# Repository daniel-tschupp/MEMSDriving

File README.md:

# OCT MEMS Scanhead

As my second project in my master studies designed a 2d OCT MEMS Scanhead.

It contained three main tasks:
* Signal processing for drifing the MEMS
* Driver electronics design
* MCU Signal generation electronics design including Software

This repository contains the entier work including a documantaion in pdf format and the presentation as a video in german.

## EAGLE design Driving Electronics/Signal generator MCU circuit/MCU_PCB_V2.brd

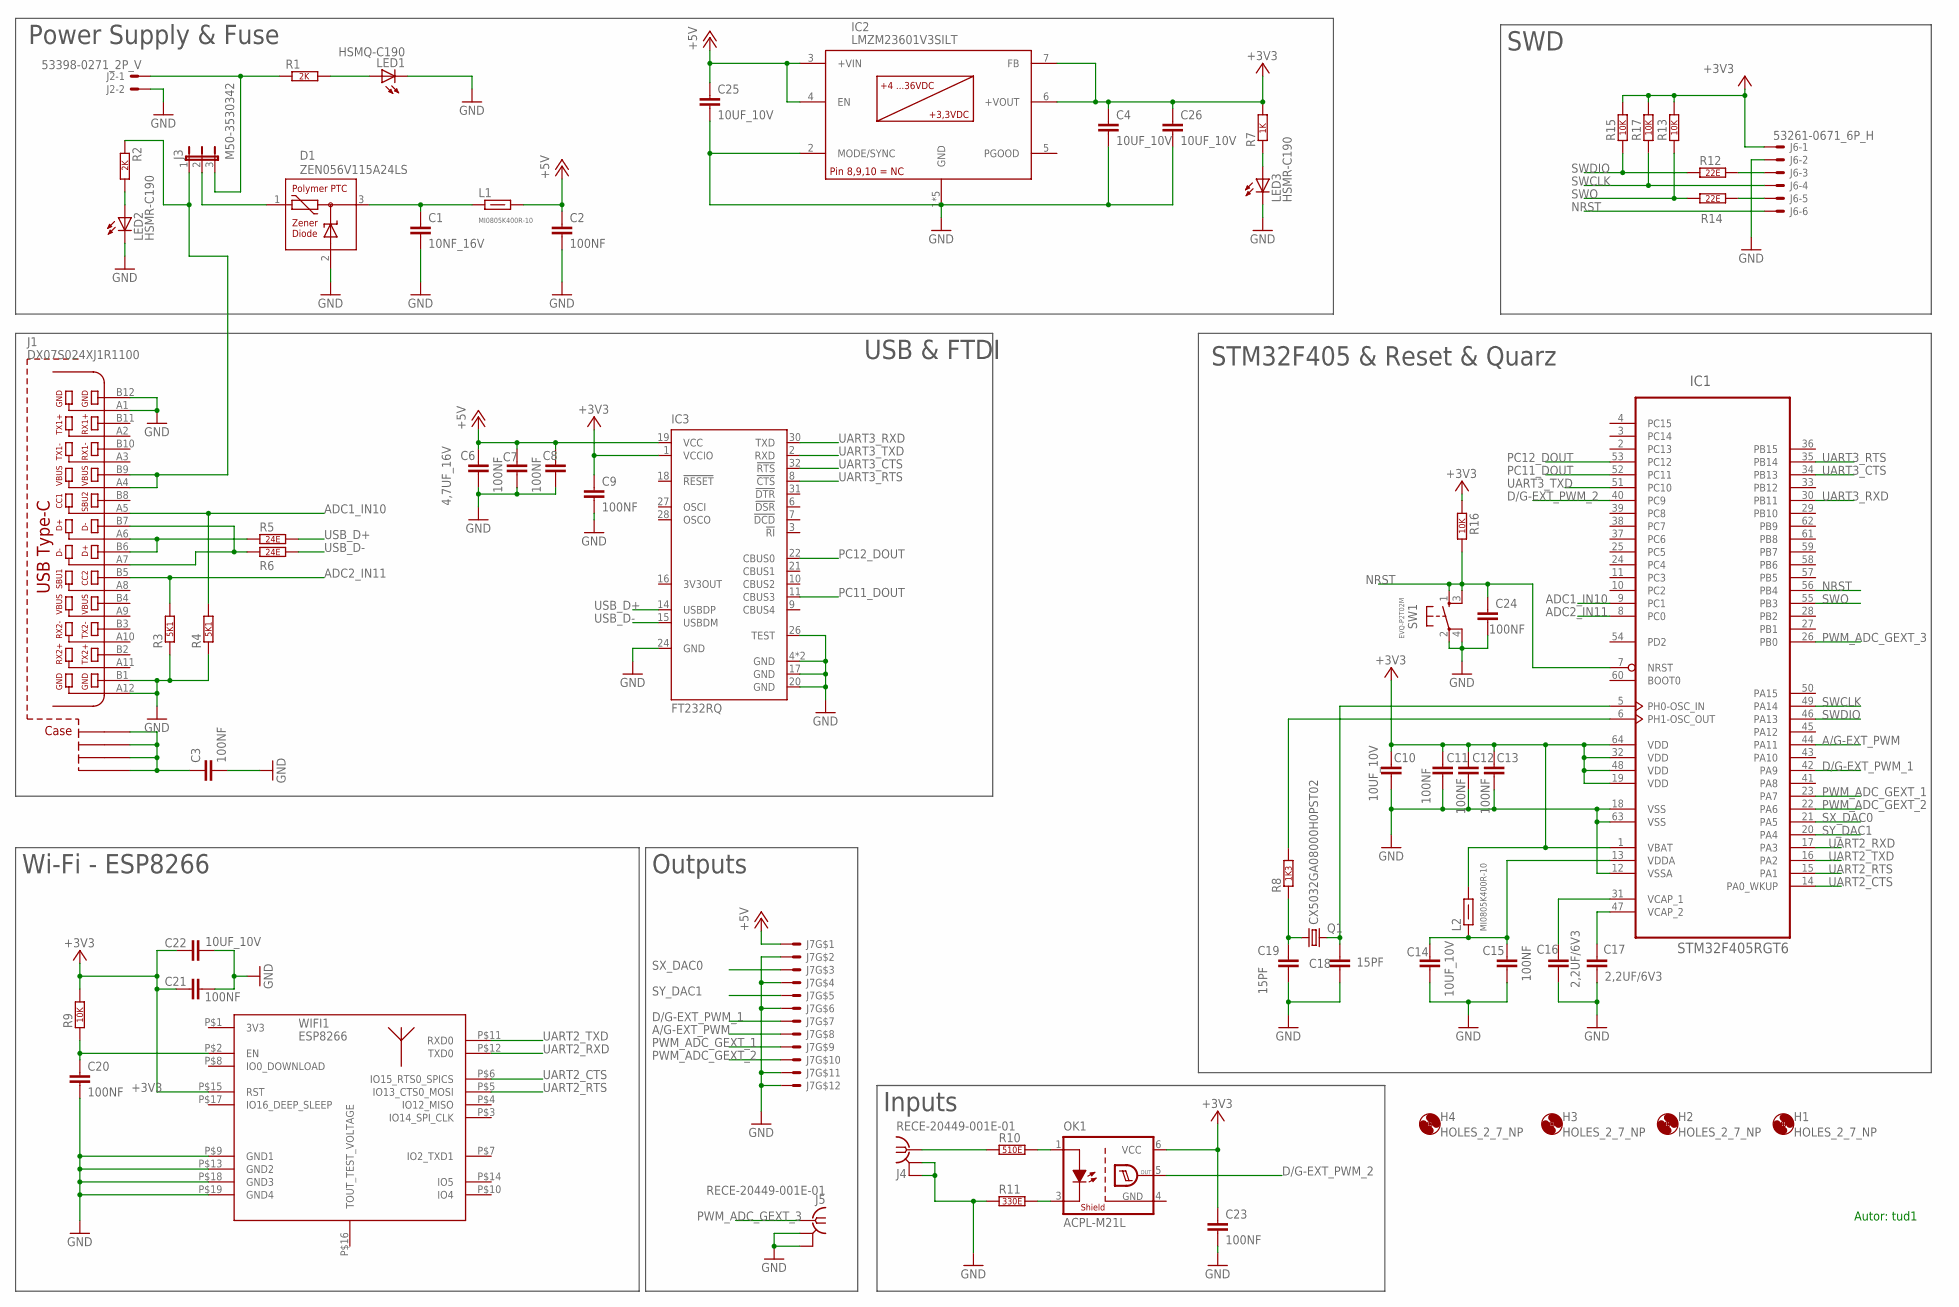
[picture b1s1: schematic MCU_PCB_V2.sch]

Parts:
C1: 10NF_16V; C0603
C2, C3, C7, C8, C9, C11, C12, C13, C15, C20, C21, C23, C24: 100NF; C0402
C4, C10, C14, C22, C25, C26: 10UF_10V; C0603
C6: 4,7UF_16V; C0603
C16, C17: 2,2UF/6V3; C0402
C18, C19: 15PF; C0402
D1: ZEN056V115A24LS; 1616_LS
H1, H2, H3, H4: HOLES_2_7_NP; 2_7_NP
IC1: STM32F405RGT6; LQFP-64
IC2: LMZM23601V3SILT; USIP-10
IC3: FT232RQ; QFN32
J1: DX07S024XJ1R1100; USB-TYPE_C_JAE
J2: 53398-0271_2P_V; 53398-02
J3: M50-3530342
J4, J5: RECE-20449-001E-01; IPEX_MHF4
J6: 53261-0671_6P_H; 53261-06
J7: 53261-7010_10P_H; 53261-10
L1, L2: MI0805K400R-10; F0805
LED1: HSMQ-C190; CHIP-LED-0603
LED2, LED3: HSMR-C190; CHIP-LED-0603
OK1: ACPL-M21L; SO-5
Q1: CX5032GA08000H0PST02; CX5032GA
R1, R2: 2K; R0603
R3, R4: 5K1; R0603
R5, R6: 24E; R0402
R7: 1K; R0603
R8: 1K3; R0402
R9, R13, R15, R16, R17: 10K; R0402
R10: 510E; R0402
R11: 330E; R0402
R12, R14: 22E; R0402
SW1: EVQ-P2T02M
WIFI1: ESP8266

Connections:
+3V3: C4.1, C9.1, C10.1, C11.1, C12.1, C13.1, C21.1, C22.1, C23.1, C26.1, IC1.1 (VBAT), IC1.19 (VDD), IC1.32 (VDD), IC1.48 (VDD), IC1.64 (VDD), IC2.6 (+VOUT), IC2.7 (FB), IC3.1 (VCCIO), J6.1, L2.2, OK1.6 (VCC), R7.2, R9.2, R13.2, R15.2, R16.1, R17.2, WIFI1.P$15 (RST)
+5V: C2.1, C6.1, C7.1, C8.1, C25.1, IC2.3 (+VIN), IC2.4 (EN), IC3.19 (VCC), J7.1, L1.2
A/G-EXT_PWM: IC1.44 (PA11), J7.8
ADC1_IN10: IC1.9 (PC1), J1.A5, R4.2
ADC2_IN11: IC1.8 (PC0), J1.B5, R3.2
D/G-EXT_PWM_1: IC1.42 (PA9), J7.7
D/G-EXT_PWM_2: IC1.40 (PC9), OK1.5 (OUT)
GND: C1.2, C2.2, C3.2, C4.2, C6.2, C7.2, C8.2, C9.2, C10.2, C11.2, C12.2, C13.2, C14.2, C15.2, C16.2, C17.2, C18.2, C19.2, C20.2, C21.2, C22.2, C23.2, C24.2, C25.2, C26.2, D1.2 (GND), IC1.12 (VSSA), IC1.18 (VSS), IC1.63 (VSS), IC2.1 (GND), IC2.2 (MODE/SYNC), IC2.GND@1 (GND), IC2.GND@2 (GND), IC2.GND@3 (GND), IC2.GND@4 (GND), IC3.4 (GND), IC3.17 (GND), IC3.20 (GND), IC3.24 (GND), IC3.26 (TEST), IC3.GND@3 (GND), J1.A1, J1.A12, J1.B1, J1.B12, J2.2, J4.2@1 (GND), J4.2@2 (GND), J4.NC (GND), J5.2@1 (GND), J5.2@2 (GND), J5.NC (GND), J6.2, J7.2, J7.4, J7.6, J7.S1, J7.S2, LED1.C, LED2.C, LED3.C, OK1.4 (GND), R3.1, R4.1, R11.1, SW1.2 (S), SW1.4 (S), WIFI1.P$9 (GND1), WIFI1.P$13 (GND2), WIFI1.P$18 (GND3), WIFI1.P$19 (GND4)
unnamed: J2.1, J3.3, R1.1
unnamed: LED1.A, R1.2
unnamed: D1.1 (VIN), J3.2
unnamed: C1.1, D1.3 (VOUT), L1.1
unnamed: LED2.A, R2.2
unnamed: C16.1, IC1.31 (VCAP_1)
unnamed: J1.A6, J1.B6, R5.1
unnamed: C17.1, IC1.47 (VCAP_2)
unnamed: C3.1, J1.C_FLEFT (S3), J1.C_FRIGHT (S1), J1.C_RLEFT (S4), J1.C_RRIGHT (S2)
unnamed: J1.A7, J1.B7, R6.1
unnamed: LED3.A, R7.1
unnamed: OK1.3 (C), R11.2
unnamed: C14.1, C15.1, IC1.13 (VDDA), L2.1
unnamed: C19.1, Q1.1, R8.1
unnamed: C18.1, IC1.5 (PH0-OSC_IN), Q1.2
unnamed: OK1.1 (A), R10.2
unnamed: J1.A4, J1.B9, J3.1, R2.1
unnamed: IC1.6 (PH1-OSC_OUT), R8.2
unnamed: J4.1, R10.1
unnamed: J6.3, R12.2
unnamed: J6.5, R14.2
NRST: C24.1, IC1.7 (NRST), IC1.56 (PB4), J6.6, R16.2, SW1.1, SW1.3
PC11_DOUT: IC1.52 (PC11), IC3.11 (CBUS3)
PC12_DOUT: IC1.53 (PC12), IC3.22 (CBUS0)
PWM_ADC_GEXT_1: IC1.23 (PA7), J7.9
PWM_ADC_GEXT_2: IC1.22 (PA6), J7.10
PWM_ADC_GEXT_3: IC1.26 (PB0), J5.1
SWCLK: IC1.49 (PA14), J6.4, R17.1
SWDIO: IC1.46 (PA13), R12.1, R15.1
SWO: IC1.55 (PB3), R13.1, R14.1
SX_DAC0: IC1.21 (PA5), J7.3
SY_DAC1: IC1.20 (PA4), J7.5
UART2_CTS: IC1.14 (PA0_WKUP), WIFI1.P$6 (IO15_RTS0_SPICS)
UART2_RTS: IC1.15 (PA1), WIFI1.P$5 (IO13_CTS0_MOSI)
UART2_RXD: IC1.17 (PA3), WIFI1.P$12 (TXD0)
UART2_TXD: IC1.16 (PA2), WIFI1.P$11 (RXD0)
UART3_CTS: IC1.34 (PB13), IC3.32 (!RTS)
UART3_RTS: IC1.35 (PB14), IC3.8 (!CTS)
UART3_RXD: IC1.30 (PB11), IC3.30 (TXD)
UART3_TXD: IC1.51 (PC10), IC3.2 (RXD)
USB_D+: IC3.14 (USBDP), R5.2
USB_D-: IC3.15 (USBDM), R6.2
WIFI_RST: C20.1, R9.1, WIFI1.P$2 (EN)

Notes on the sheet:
Power Supply & Fuse
USB & FTDI
SWD
STM32F405 & Reset & Quarz
Wi-Fi - ESP8266
Outputs
Inputs
Autor: tud1

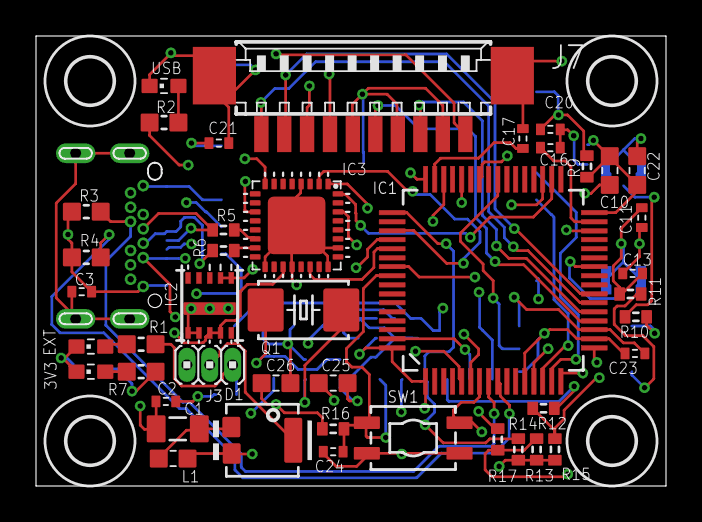
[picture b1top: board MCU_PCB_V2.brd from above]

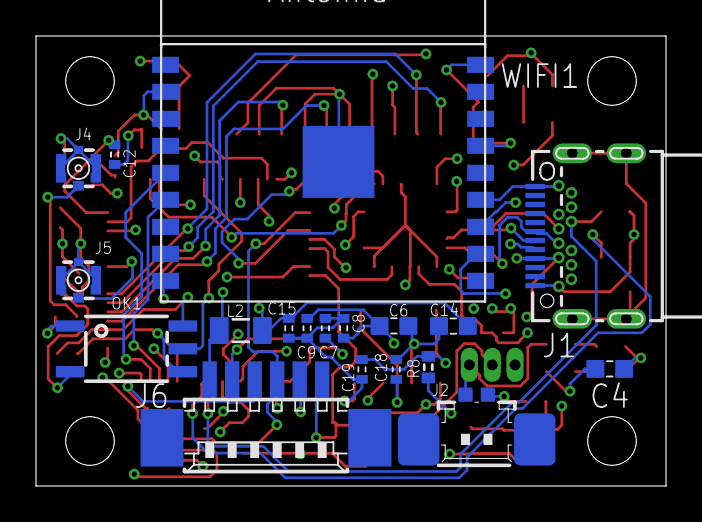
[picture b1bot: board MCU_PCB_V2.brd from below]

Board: 4 copper layers, 35.0 x 25.0 mm, 66 parts (19 on the bottom side), 51 nets.

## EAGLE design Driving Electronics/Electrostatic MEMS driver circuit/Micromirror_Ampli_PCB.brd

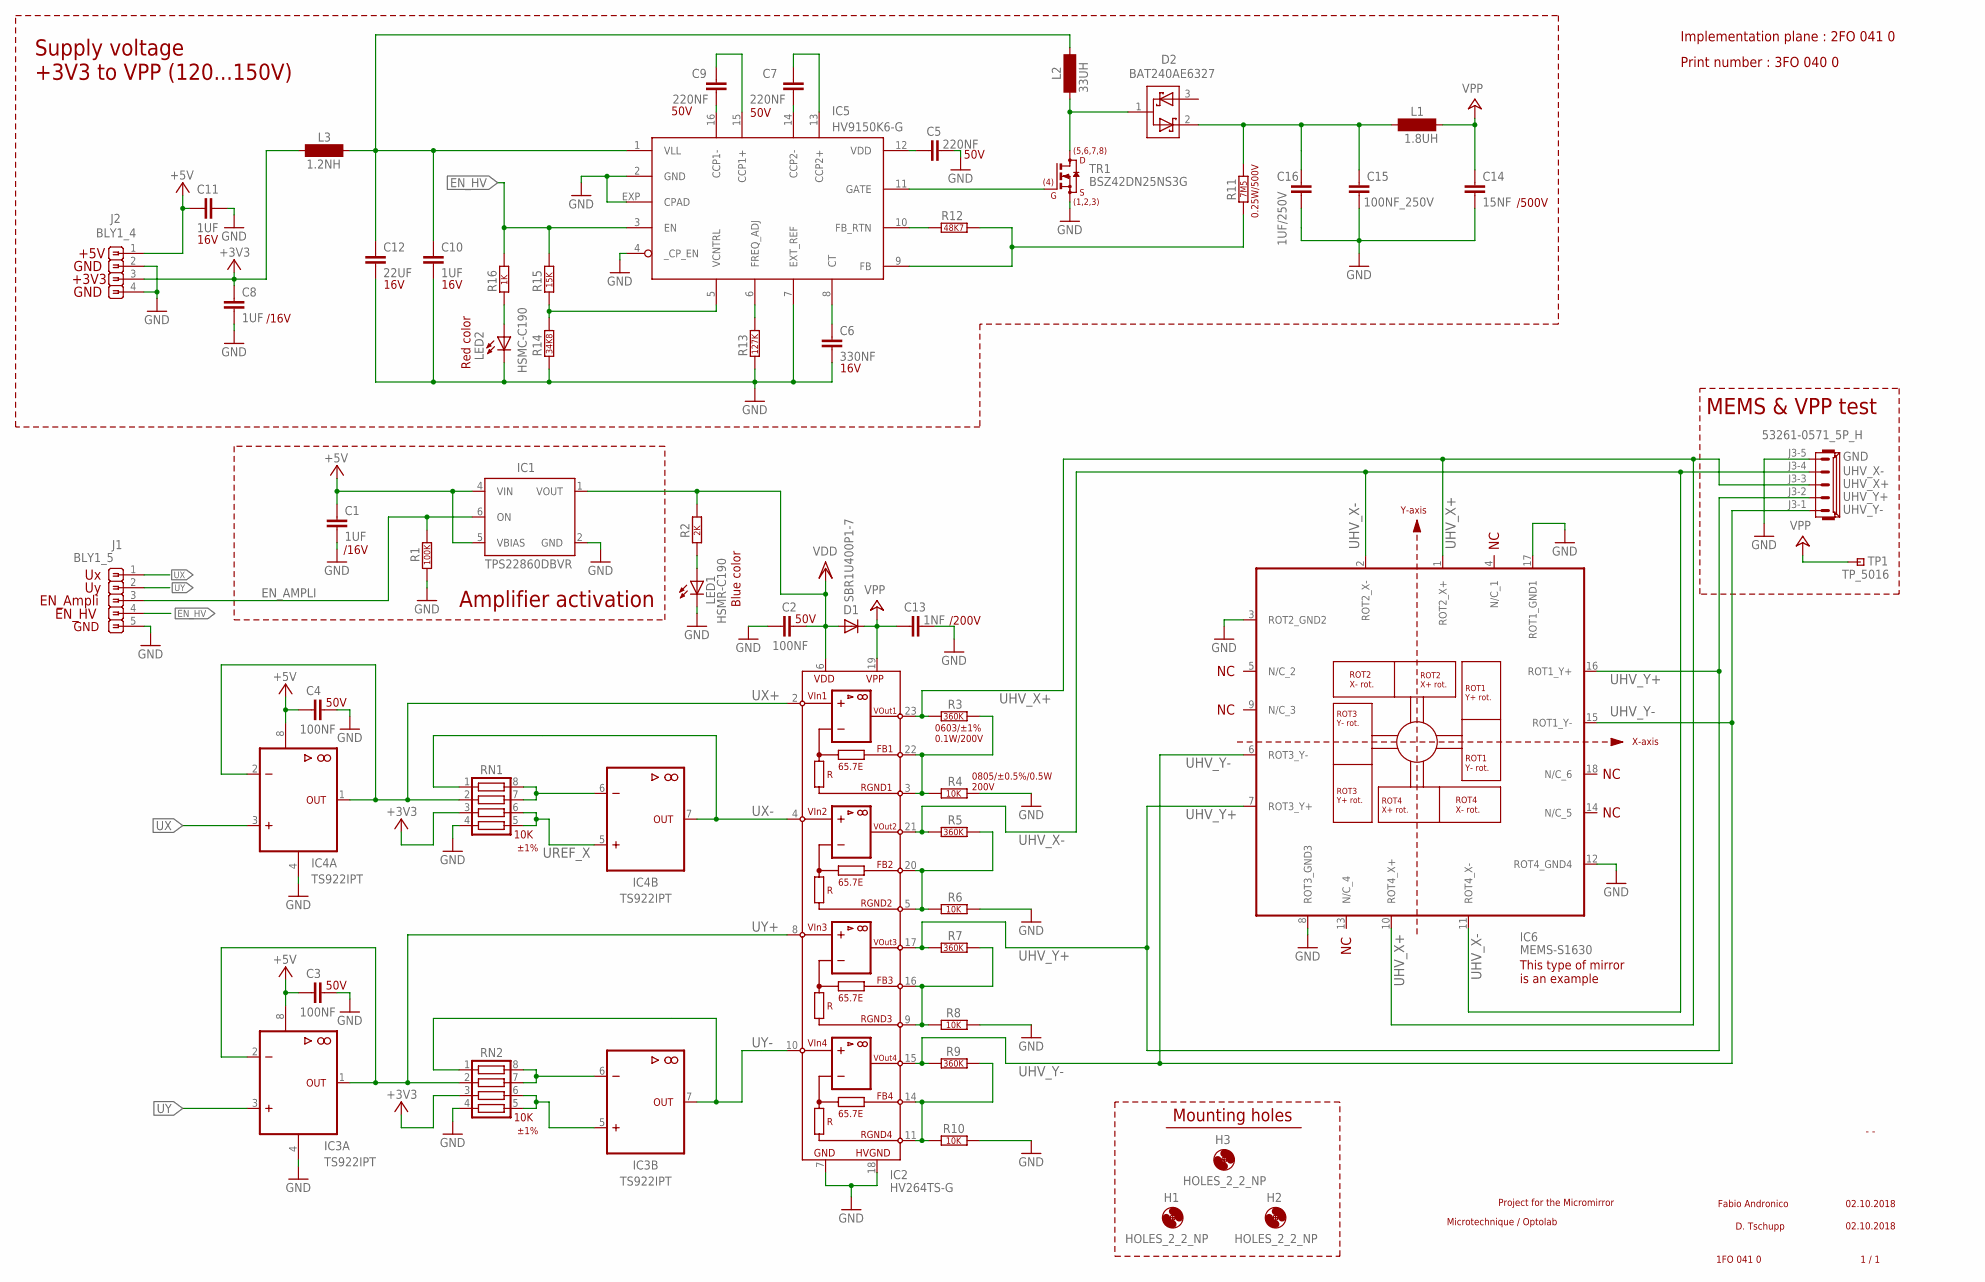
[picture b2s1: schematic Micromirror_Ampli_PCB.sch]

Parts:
C1, C8, C10, C11: 1UF; C0603
C2, C3, C4: 100NF; C0603
C5, C7, C9: 220NF; C0603
C6: 330NF; C0603
C12: 22UF; C0805
C13: 1NF; C0603
C14: 15NF; C0805
C15: 100NF_250V; C0805
C16: 1UF/250V; C1812
D1: SBR1U400P1-7; POWERDI_123
D2: BAT240AE6327; SOT23-3
H1, H2, H3: HOLES_2_2_NP; 2_2_NP
IC1: TPS22860DBVR; SOT23-6
IC2: HV264TS-G; TSSOP24
IC3, IC4: TS922IPT; TSSOP8
IC5: HV9150K6-G; QFN16
IC6: MEMS-S1630; LCC18
J1: BLY1_5; BLY1_5_2MM
J2: BLY1_4; BLY1_4_2MM
J3: 53261-0571_5P_H; 53261-05
L1: 1.8UH; L0805
L2: 33UH; NR5040
L3: 1.2NH; L08051R2CEWTR
LED1: HSMR-C190; CHIP-LED-0603
LED2: HSMC-C190; CHIP-LED-0603
R1: 100K; R0603
R2: 2K; R0603
R3, R5, R7, R9: 360K; R0603
R4, R6, R8, R10: 10K_0.5%; R0805
R11: 7M5; R1206
R12: 48K7; R0603
R13: 127K; R0603
R14: 34K8; R0603
R15: 15K; R0603
R16: 1K_0.1W; R0603
RN1, RN2: 10K; RN1206
TP1: TP_5016; 5016
TR1: BSZ42DN25NS3G; TSDSON-8

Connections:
+3V3: C8.1, J2.3, L3.1, RN1.3, RN2.3
+5V: C1.1, C3.1, C4.1, C11.1, IC1.4 (VIN), IC1.5 (VBIAS), IC3.8 (+5V), IC4.8 (+5V), J2.1
EN_AMPLI: IC1.6 (ON), J1.3, R1.1
EN_HV: IC5.3 (EN), J1.4, R15.2, R16.2
GND: C1.2, C2.2, C3.2, C4.2, C5.1, C6.2, C8.2, C10.2, C11.2, C12.2, C13.2, C14.2, C15.2, C16.2, IC1.2 (GND), IC2.7 (GND), IC2.18 (HVGND), IC3.4 (GND), IC4.4 (GND), IC5.2 (GND), IC5.4 (_CP_EN), IC5.7 (EXT_REF), IC5.EXP (CPAD), IC6.3 (ROT2_GND2), IC6.8 (ROT3_GND3), IC6.12 (ROT4_GND4), IC6.17 (ROT1_GND1), J1.5, J2.2, J2.4, J3.5, LED1.C, LED2.C, R1.2, R4.2, R6.2, R8.2, R10.2, R13.1, R14.1, RN1.4, RN2.4, TR1.1 (S), TR1.2 (S), TR1.3 (S)
unnamed: IC5.11 (GATE), TR1.4 (G)
unnamed: C9.1, IC5.16 (CCP1-)
unnamed: C9.2, IC5.15 (CCP1+)
unnamed: C7.2, IC5.14 (CCP2-)
unnamed: C7.1, IC5.13 (CCP2+)
unnamed: C5.2, IC5.12 (VDD)
unnamed: IC5.5 (VCNTRL), R14.2, R15.1
unnamed: IC5.6 (FREQ_ADJ), R13.2
unnamed: C6.1, IC5.8 (CT)
unnamed: D2.1, L2.1, TR1.5 (D)
unnamed: IC5.10 (FB_RTN), R12.1
unnamed: C15.1, C16.1, D2.2, L1.1, R11.2
unnamed: IC5.9 (FB), R11.1, R12.2
unnamed: IC3.6 (-IN), RN2.7, RN2.8
unnamed: IC3.5 (+IN), RN2.5, RN2.6
unnamed: LED2.A, R16.1
unnamed: IC2.3 (RGND1), IC2.22 (FB1), R3.2, R4.1
unnamed: IC4.6 (-IN), RN1.7, RN1.8
unnamed: IC2.5 (RGND2), IC2.20 (FB2), R5.2, R6.1
unnamed: LED1.A, R2.1
unnamed: C10.1, C12.1, IC5.1 (VLL), L2.2, L3.2
unnamed: IC2.9 (RGND3), IC2.16 (FB3), R7.2, R8.1
unnamed: IC2.11 (RGND4), IC2.14 (FB4), R9.2, R10.1
UHV_X+: IC2.23 (VOUT1), IC6.1 (ROT2_X+), IC6.10 (ROT4_X+), J3.3, R3.1
UHV_X-: IC2.21 (VOUT2), IC6.2 (ROT2_X-), IC6.11 (ROT4_X-), J3.4, R5.1
UHV_Y+: IC2.17 (VOUT3), IC6.7 (ROT3_Y+), IC6.16 (ROT1_Y+), J3.2, R7.1
UHV_Y-: IC2.15 (VOUT4), IC6.6 (ROT3_Y-), IC6.15 (ROT1_Y-), J3.1, R9.1
UREF_X: IC4.5 (+IN), RN1.5, RN1.6
UX: IC4.3 (+IN), J1.1
UX+: IC2.2 (+VIN1), IC4.1 (OUT), IC4.2 (-IN), RN1.2
UX-: IC2.4 (+VIN2), IC4.7 (OUT), RN1.1
UY: IC3.3 (+IN), J1.2
UY+: IC2.8 (+VIN3), IC3.1 (OUT), IC3.2 (-IN), RN2.2
UY-: IC2.10 (+VIN4), IC3.7 (OUT), RN2.1
VDD: C2.1, D1.A, IC1.1 (VOUT), IC2.6 (VDD), R2.2
VPP: C13.1, C14.1, D1.C, IC2.19 (VPP), L1.2, TP1.1

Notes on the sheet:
Fabio Andronico
02.10.2018
1FO 041 0
1 / 1
- -
Microtechnique / Optolab
Project for the Micromirror
D. Tschupp
Print number : 3FO 040 0
Implementation plane : 2FO 041 0
+5V
GND
+3V3
EN_HV
EN_Ampli
Supply voltage +3V3 to VPP (120...150V)
Amplifier activation
MEMS & VPP test
Mounting holes
0603/±1% 0.1W/200V
0805/±0.5%/0.5W 200V
0.25W/500V
Blue color
Red color
/200V
/500V
This type of mirror is an example
±1%
/16V
16V
50V

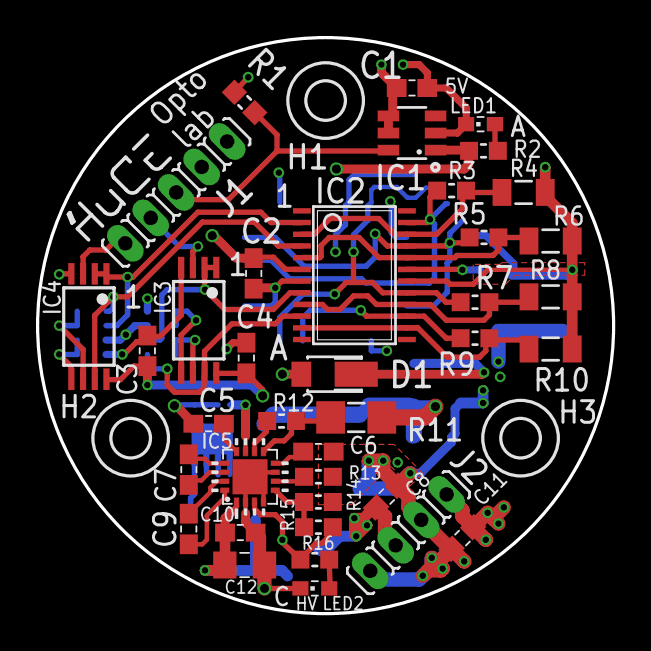
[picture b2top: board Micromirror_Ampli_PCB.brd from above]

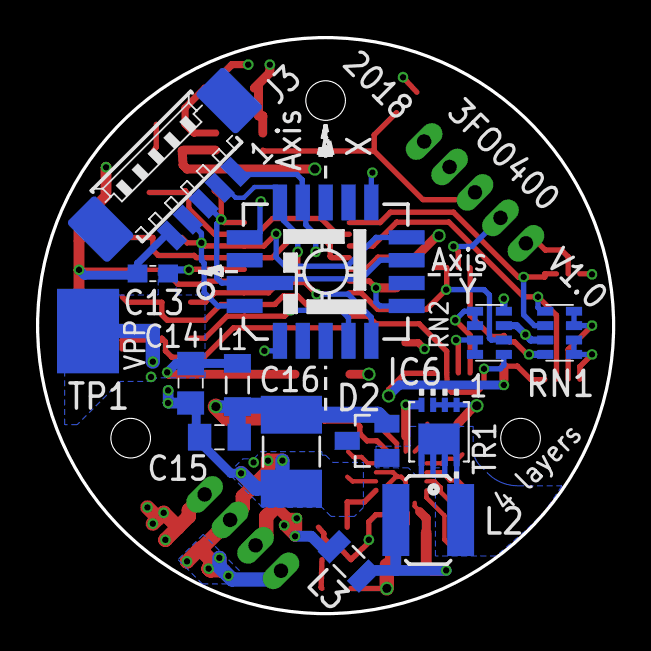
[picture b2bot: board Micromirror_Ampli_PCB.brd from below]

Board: 4 copper layers, 32.0 x 32.0 mm, 66 parts (14 on the bottom side), 41 nets.

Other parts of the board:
DRILEGEND: DRILEGEND
U$2: DIN_A4_L_LOC_LAYER_TOP
U$3: DIN_A4_L_LOC_INNERLAYER2
U$4: DIN_A4_L_LOC_SILKSCREEN_TOP
U$5: DIN_A4_L_LOC_LAYER_BOTTOM
U$6: DIN_A4_L_LOC_SILKSCREEN_BOTTOM
U$7: DIN_A4_L_LOC_INNERLAYER3
U$8: DIN_A4_L_LOC_DRILL_BFH
U$9: COUPE_4L_1,6
U$10: DIN_A4_L_LOC_TOP_DOCU
U$11: DIN_A4_L_LOC_BOTTOM_DOCU

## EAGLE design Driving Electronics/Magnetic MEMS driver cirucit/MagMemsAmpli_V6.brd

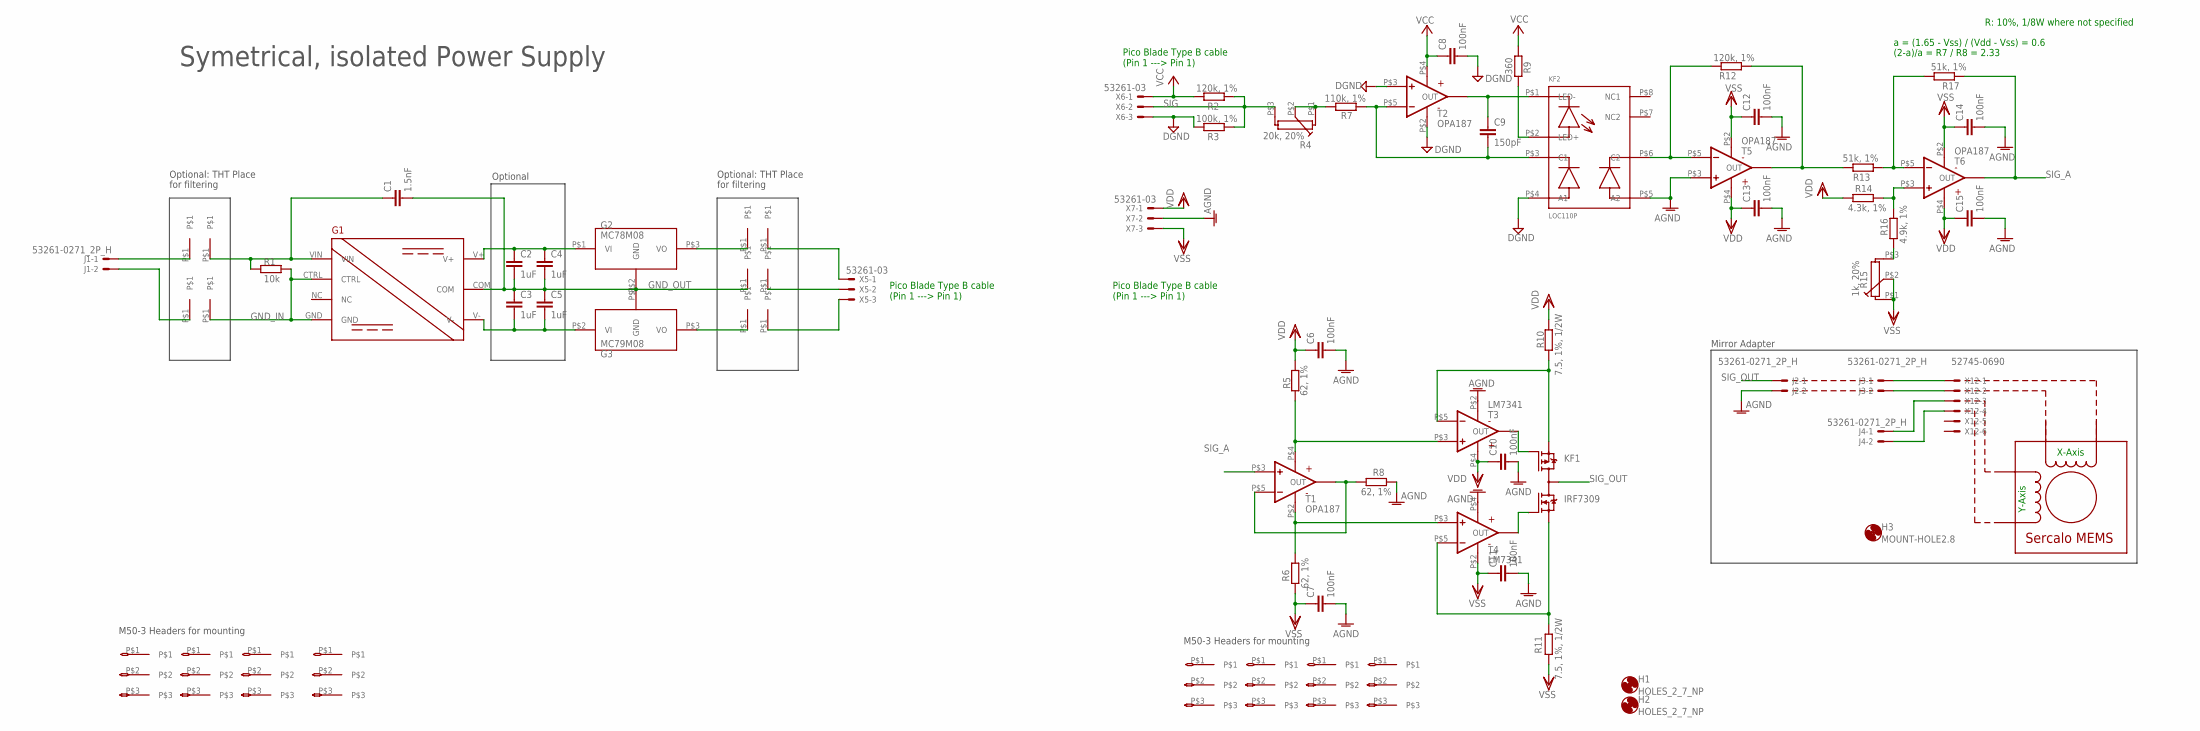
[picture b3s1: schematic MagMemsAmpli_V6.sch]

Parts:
C1: 1.5nF; C0805K; MOUSER 0805B152K500CT
C2, C3, C4, C5: 1uF; C0805K; MOUSER 0805B105K500CT
C6, C7, C8, C10, C11, C12, C13, C14, C15: 100nF; C0603K; MOUSER 06033C104KAT4A
C9: 150pF; C0603K; MOUSER C0603C101M5HACTU
G1: RS6-0512D; RS_THT
G2: MC78M08; DPAK-3; MOUSER MC78M08CDTG
G3: MC79M08; DPAK-3
H1, H2: HOLES_2_7_NP; 2_7_NP
H3: MOUNT-HOLE2.8; 2,8
J1, J2, J3, J4: 53261-0271_2P_H; 53261-02
KF1: IRF7309; SO08-IRF
KF2: LOC110P
R1: 10k; R0603; MOUSER ESR03EZPF62R0
R2, R12: 120k, 1%; R0603; MOUSER MCT06030C1203FP500
R3: 100k, 1%; R0603; MOUSER MCT06030C1003FP500
R4: 20k, 20%; SM-3T; MOUSER SM-3TW203
R5, R6, R8: 62, 1%; R0603; MOUSER ESR03EZPF62R0
R7: 110k, 1%; R0603; MOUSER CRCW0603110KFKEAC
R9: 360; R0603; MOUSER MR06X3600FTL
R10, R11: 7.5, 1%, 1/2W; R0805; MOUSER ESR10EZPF7R50
R13, R17: 51k, 1%; R0603; MOUSER MCT06030C5102FP500
R14: 4.3k, 1%; R0603; MOUSER SDR03EZPF4301
R15: 1k, 20%; SM-3T; MOUSER SM-3TW102
R16: 4.9k, 1%; R0603; MOUSER MCT0603MC4701FP500
T1, T2, T5, T6: OPA187; SOT23-5
T3, T4: LM7341; SOT23-5
TP1, TP2, TP3, TP4, TP5, TP6, TP7, TP8, TP9, TP10: TP10
X1, X2, X3, X4: M50-3; MOUSER M50-3030342
X5, X6, X7: 53261-03; MOUSER 53261-0371
X8, X9, X10, X11: M50-3; MOUSER M50-3530342
X12: 52745-0690; MOUSER 52745-0697

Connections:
AGND: C6.2, C7.2, C10.2, C11.2, C12.2, C13.2, C14.2, C15.2, J2.2, KF2.P$5 (A2), R8.1, T3.P$2 (V-), T4.P$4 (V+), T5.P$3 (+IN), X7.2
DGND: C8.2, KF2.P$4 (A1), R3.2, T2.P$2 (V-), T2.P$3 (+IN), X6.3
GND_IN: G1.CTRL, G1.GND, R1.2, TP4.P$1
GND_OUT: C1.2, C2.2, C3.1, C4.2, C5.1, G1.COM, G2.P$2 (GND), G3.P$1 (GND), TP6.P$1
unnamed: C1.1, G1.VIN, R1.1, TP3.P$1
unnamed: C2.1, C4.1, G1.V+, G2.P$1 (VI)
unnamed: C3.2, C5.2, G1.V-, G3.P$2 (VI)
unnamed: J1.1, TP1.P$1
unnamed: J1.2, TP2.P$1
unnamed: C9.1, KF2.P$1 (LED-), T2.P$1 (OUT)
unnamed: KF2.P$2 (LED+), R9.1
unnamed: R13.1, R17.2, T6.P$5 (-IN)
unnamed: R12.1, R13.2, T5.P$1 (OUT)
unnamed: C9.2, KF2.P$3 (C1), R7.2, T2.P$5 (-IN)
unnamed: KF2.P$6 (C2), R12.2, T5.P$5 (-IN)
unnamed: R14.2, R16.2, T6.P$3 (+IN)
unnamed: G2.P$3 (VO), TP5.P$1
unnamed: G3.P$3 (VO), TP7.P$1
unnamed: TP8.P$1, X5.1
unnamed: TP9.P$1, X5.2
unnamed: TP10.P$1, X5.3
unnamed: KF1.3 (P-S), R10.1, T3.P$5 (-IN)
unnamed: KF1.4 (P-G), T3.P$1 (OUT)
unnamed: KF1.2 (N-G), T4.P$1 (OUT)
unnamed: KF1.1 (N-S), R11.2, T4.P$5 (-IN)
unnamed: R8.2, T1.P$1 (OUT), T1.P$5 (-IN)
unnamed: R6.2, T1.P$2 (V-), T4.P$3 (+IN)
unnamed: R5.1, T1.P$4 (V+), T3.P$3 (+IN)
unnamed: J3.1, X12.1
unnamed: J3.2, X12.2
unnamed: J4.1, X12.3
unnamed: J4.2, X12.4
unnamed: R4.P$1 (1A), R4.P$2 (1S), R7.1
unnamed: R15.P$3 (1E), R16.1
SIG: R2.1, R3.1, R4.P$3 (1E), X6.2
SIG_A: R17.1, T1.P$3 (+IN), T6.P$1 (OUT)
SIG_OUT: J2.1, KF1.5 (D), KF1.6 (D), KF1.7 (D), KF1.8 (D)
VCC: C8.1, R2.2, R9.2, T2.P$4 (V+), X6.1
VDD: C6.1, C10.1, C13.1, C15.1, R5.2, R10.2, R14.1, T3.P$4 (V+), T5.P$4 (V+), T6.P$4 (V+), X7.1
VSS: C7.1, C11.1, C12.1, C14.1, R6.1, R11.1, R15.P$1 (1A), R15.P$2 (1S), T4.P$2 (V-), T5.P$2 (V-), T6.P$2 (V-), X7.3

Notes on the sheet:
(2-a)/a = R7 / R8 = 2.33
X-Axis
Y-Axis
R: 10%, 1/8W where not specified
Pico Blade Type B cable (Pin 1 ---> Pin 1)
Optional
Optional: THT Place
for filtering
M50-3 Headers for mounting
Mirror Adapter
Symetrical, isolated Power Supply
a = (1.65 - Vss) / (Vdd - Vss) = 0.6

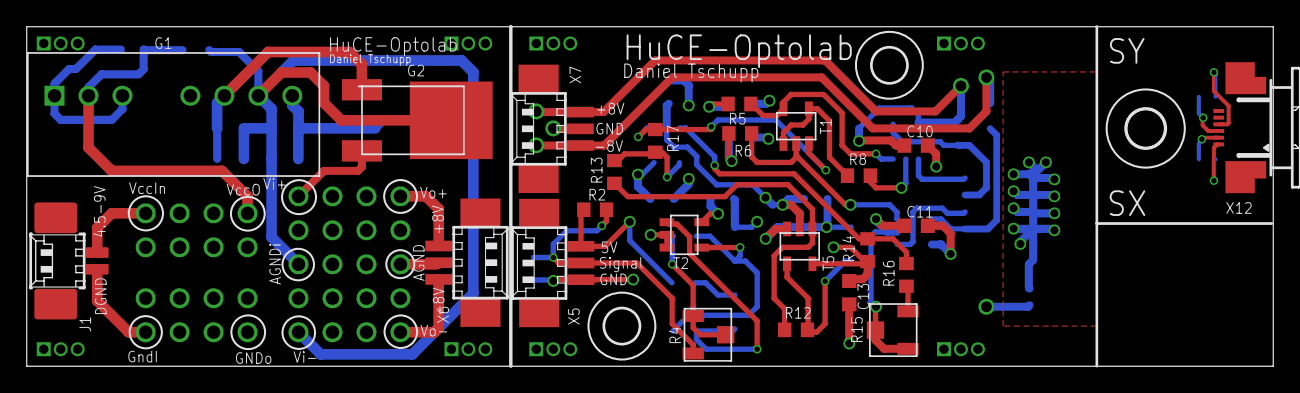
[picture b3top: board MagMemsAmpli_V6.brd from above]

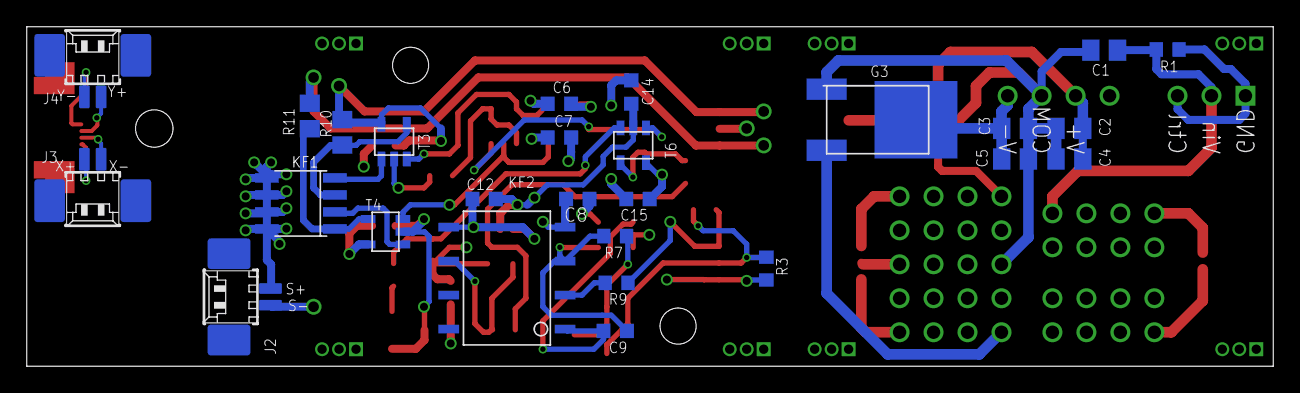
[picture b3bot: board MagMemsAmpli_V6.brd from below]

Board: 4 copper layers, 93.2 x 25.4 mm, 72 parts (27 on the bottom side), 40 nets.

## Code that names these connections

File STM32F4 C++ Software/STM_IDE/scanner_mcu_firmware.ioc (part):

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Mcu.Name=STM32F405RGTx
Mcu.Package=LQFP64
Mcu.UserName=STM32F405RGTx
PA0-WKUP.GPIOParameters=GPIO_PuPd
PA0-WKUP.GPIO_PuPd=GPIO_PULLDOWN
PA0-WKUP.Signal=GPIO_Output
PA13.Mode=Trace_Asynchronous_SW
PA13.Signal=SYS_JTMS-SWDIO
PA14.Mode=Trace_Asynchronous_SW
PA14.Signal=SYS_JTCK-SWCLK
PA2.Mode=Asynchronous
PA2.Signal=USART2_TX
PA3.Mode=Asynchronous
PA3.Signal=USART2_RX
PA4.GPIOParameters=GPIO_Label
PA4.GPIO_Label=DAC_OUT1_UX
PA4.Signal=COMP_DAC1_group
PA5.GPIOParameters=GPIO_Label
PA5.GPIO_Label=DAC_OUT2_UY
PA5.Signal=COMP_DAC2_group
PA9.Signal=S_TIM1_CH2
PB0.Signal=S_TIM3_CH3
PB11.Mode=Asynchronous
PB11.Signal=USART3_RX
PB3.Mode=Trace_Asynchronous_SW
PB3.Signal=SYS_JTDO-SWO
PC10.Mode=Asynchronous
PC10.Signal=USART3_TX
PC11.GPIOParameters=GPIO_Label
PC11.GPIO_Label=CBUS3
PC11.Signal=GPIO_Output
PC12.GPIOParameters=GPIO_Label
PC12.GPIO_Label=CBUS0
PC12.Signal=GPIO_Output
PH0-OSC_IN.Mode=HSE-External-Oscillator
PH0-OSC_IN.Signal=RCC_OSC_IN
PH1-OSC_OUT.Mode=HSE-External-Oscillator
PH1-OSC_OUT.Signal=RCC_OSC_OUT
RCC.HSE_VALUE=8000000
RCC.SYSCLKFreq_VALUE=168000000
RCC.SYSCLKSource=RCC_SYSCLKSOURCE_PLLCLK
board=custom

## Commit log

2021-05-23 uploaded the MEMS driving project
2021-05-23 dnt upload compressed project presentation
2021-05-23 dnt changed documentation name
2021-05-23 dnt readme
